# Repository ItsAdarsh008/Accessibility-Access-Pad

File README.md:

# AccessibilityAccessPad by Adarsh

AAPad is an 8 key macropad with a rotary encoder, an OLED Display. It also has 9 WS2812B Leds, and uses QMK firmware

It serves as a plug & play device integrated with the Windows accessibility toolkit in order to allow computer-illiterate users use of accessibility features (i.e. high contrast mode). 

## Features:
- Dual layer PLA case (hopefully made out of wood, later)
- Plexiglass window, displaying the diodes and silkscreened logo on the PCB (also my glasses )
- 128x32 OLED Display, to allow bystanders to assist the user whenever necessary
- EC11 Rotary encoder, for tactile feedback
- 9 WS2812B RGB LEDs. One for the accessibility icon, and the rest for backlighting
- 8 Keys (for functions, see below)

## Planned Features:
- [VIA](https://www.caniusevia.com/) support!
- Reactive backlight for each key

## CAD Model:
Everything fits together using 6 M3 Bolts and heatset inserts. 4 for the case, two for the PCB.

It has 2 separate printed pieces. The base, where the PCB is mounted, and the cover.

Made in Fusion360. First time using it!

## PCB
Here's my PCB! It was made in KiCad. The silkscreen(s) was imported from Canva. I also put a quote on the top right, because why not?

Schematic

PCB

## Firmware Overview
This hackpad uses [QMK](https://qmk.fm/) firmware for everything. 

- The rotary encoder changes volume, press to mute

- The 8 keys currently act as functions/macros I preassigned in QMK.
    1. Text-to-Speech (TTS) Toggle
        - Reads aloud selected text on screen
    2. Zoom In
    3. Zoom Out
    4. Speech-to-Text Activation
        - Starts or stops dictation mode to convert speech into text
    5. Adjusts Cursor Speed
    6. Activates Computer speakers to announce a custom message (preset "I need assistance")
    7. High Contrast Mode Toggle
    8. Opens Accessibility Settings Window

- The OLED reads out the function of a button whenever it is pressed. The goal is so that any bystander who is called to assist the user may know what the device is suppose to be doing at any given input.

- *Note*: **Please suggest any new functions for each key!!** I have a very limited understanding of accessibility needs at the moment, though I hope my preset functions serve you well.

## BOM:
Here should be everything you need to make this hackpad

- 8x Cherry MX Style Switches
- 8x DSA Keycaps
- 6x M3x5x4 Heatset inserts
- 3x M3x16mm SHCS Bolts
- 9x 1N4148 DO-35 Diodes.
- 9x WS2812B LEDs
- 1x 0.91" 128x32 OLED Display
- 1x EC11 Rotary Encoder
- 1x XIAO RP2040
- 1x Case (2 printed parts, PLA)

## Extra stuff
Thanks so much for reading to the end, this is my first real hardware project. Stay tuned to my GitHub for more :\)\)

~ Adarsh

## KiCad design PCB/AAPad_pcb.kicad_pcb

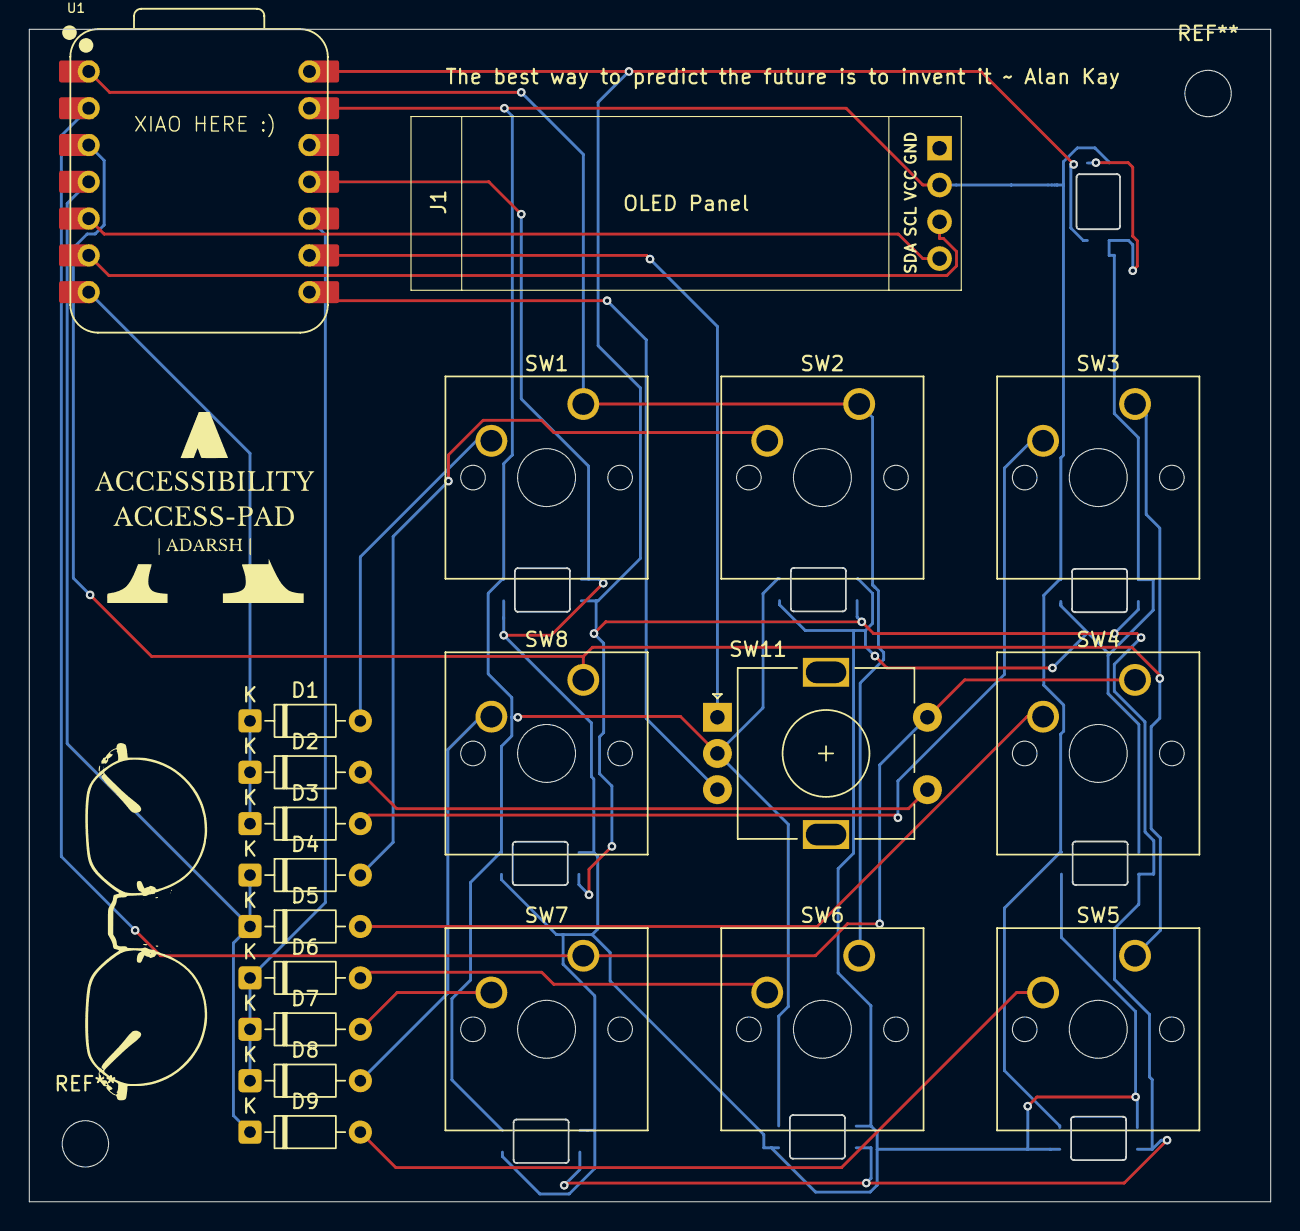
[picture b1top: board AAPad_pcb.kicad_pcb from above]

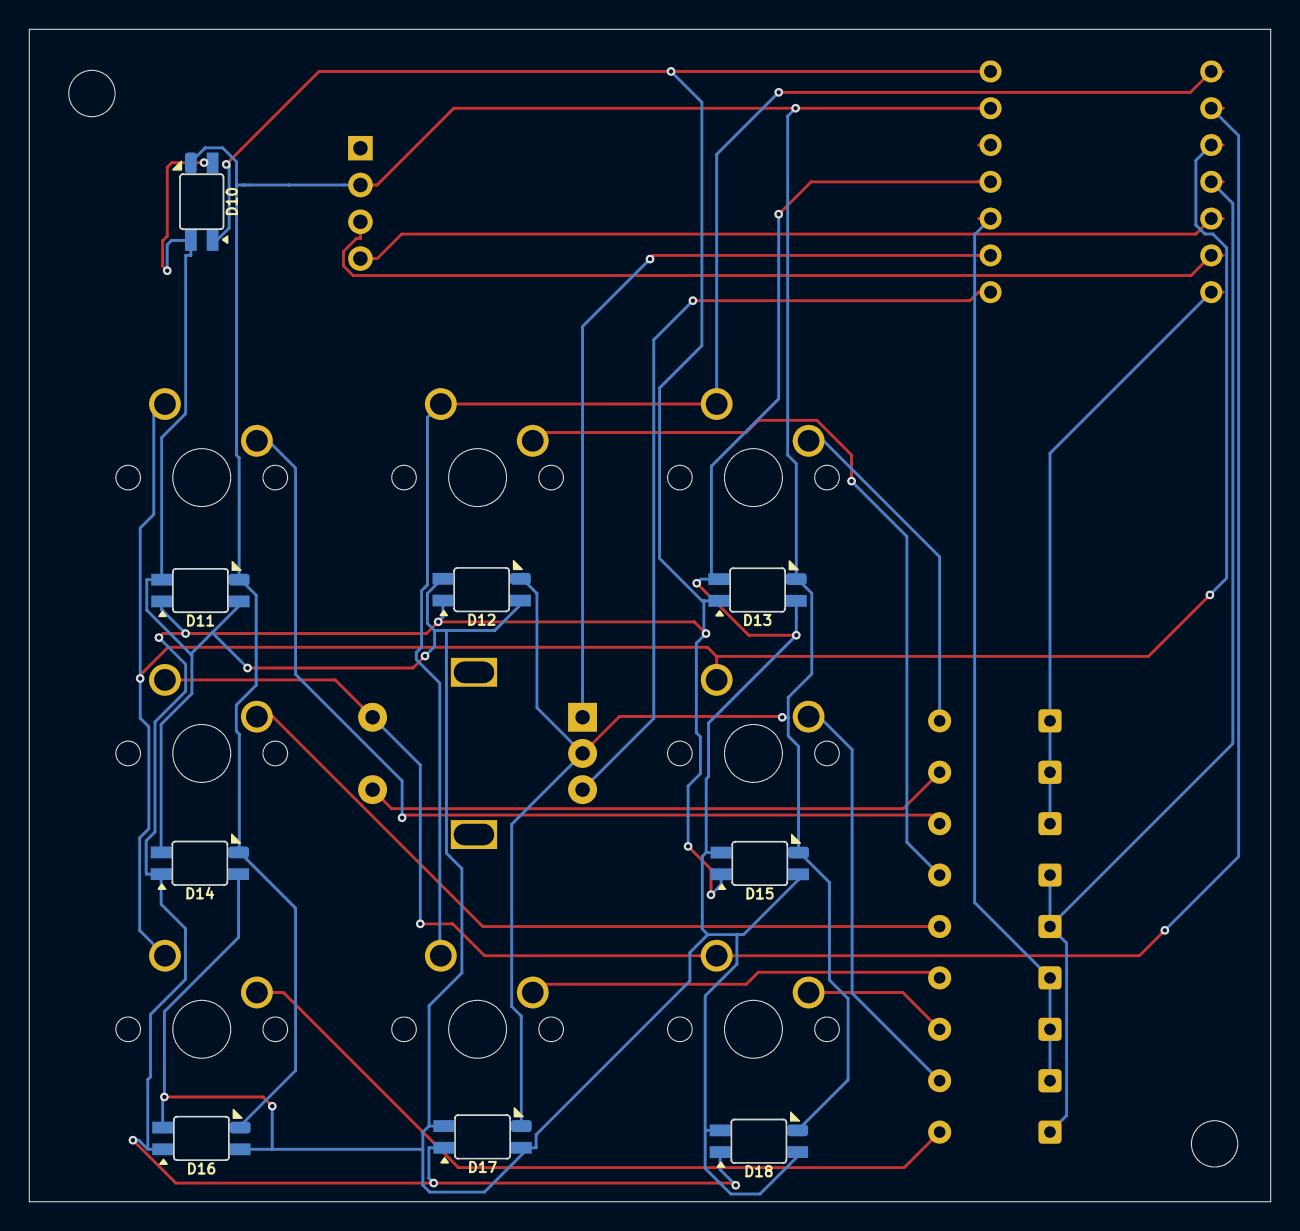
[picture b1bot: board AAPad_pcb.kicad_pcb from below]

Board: 2 copper layers, 85.7 x 81.0 mm, 29 parts (9 on the bottom side), 22 nets.

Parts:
D1, D2, D3, D4, D5, D6, D7, D8, D9: 1N4148WT; D_DO-35_SOD27_P7.62mm_Horizontal
D10, D11, D12, D13, D14, D15, D16, D17, D18: WS2812B; SK6812-MINI-E
J1: OLED_DISPLAY; SSD1306-0.91-OLED-4pin-128x32
SW1, SW2, SW3, SW4, SW5, SW6, SW7, SW8: SW_Push_45deg; SW_Cherry_MX_1.00u_PCB
SW11: RotaryEncoder_Switch; RotaryEncoder_Alps_EC11E-Switch_Vertical_H20mm
U1: XIAO-RP2040-DIP

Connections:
+5V: D10.1 (VDD), D11.1 (VDD), D12.1 (VDD), D13.1 (VDD), D14.1 (VDD), D15.1 (VDD), D16.1 (VDD), D17.1 (VDD), D18.1 (VDD), U1.14 (VBUS)
Col 0: SW1.1, SW2.1, SW6.1, U1.1 (GPIO26/ADC0/A0)
Col 1: SW4.1, SW7.1, SW11.S2, U1.2 (GPIO27/ADC1/A1)
Col 2: SW3.1, SW5.1, SW8.1, U1.3 (GPIO28/ADC2/A2)
EC11A: SW11.A, U1.9 (GPIO2/SCK)
EC11B: SW11.B, U1.8 (GPIO1/RX)
EC11SWB: D2.2 (A), SW11.S1
GND: D10.3 (VSS), D11.3 (VSS), D12.3 (VSS), D13.3 (VSS), D14.3 (VSS), D15.3 (VSS), D16.3 (VSS), D17.3 (VSS), D18.3 (VSS), J1.2, SW11.C, U1.13 (GND)
unnamed: D1.2 (A), SW1.2
unnamed: D3.2 (A), SW3.2
unnamed: D4.2 (A), SW2.2
unnamed: D5.2 (A), SW4.2
unnamed: D6.2 (A), SW6.2
unnamed: D7.2 (A), SW7.2
unnamed: D8.2 (A), SW8.2
unnamed: D9.2 (A), SW5.2
Row 0: D4.1 (K), D5.1 (K), D9.1 (K), U1.4 (GPIO29/ADC3/A3)
Row 1: D1.1 (K), D2.1 (K), D3.1 (K), U1.7 (GPIO0/TX)
Row 2: D6.1 (K), D7.1 (K), D8.1 (K), U1.10 (GPIO4/MISO)
SCL: J1.3, U1.6 (GPIO7/SCL)
SDA: J1.4, U1.5 (GPIO6/SDA)
WS2812B: D10.2 (DOUT), D10.4 (DIN), D11.2 (DOUT), D11.4 (DIN), D12.2 (DOUT), D12.4 (DIN), D13.2 (DOUT), D13.4 (DIN), D14.2 (DOUT), D14.4 (DIN), D15.2 (DOUT), D15.4 (DIN), D16.2 (DOUT), D16.4 (DIN), D17.2 (DOUT), D17.4 (DIN), D18.2 (DOUT), D18.4 (DIN), U1.11 (GPIO3/MOSI)

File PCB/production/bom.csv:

Designator,Footprint,Quantity,Value,LCSC Part #
"D1, D2, D3, D4, D5, D6, D7, D8, D9",D_DO-35_SOD27_P7.62mm_Horizontal,9,1N4148WT,
"D10, D11, D12, D13, D14, D15, D16, D17, D18",SK6812-MINI-E,9,WS2812B,
J1,SSD1306-0.91-OLED-4pin-128x32,1,OLED_DISPLAY,
"SW1, SW2, SW3, SW4, SW5, SW6, SW7, SW8",SW_Cherry_MX_1.00u_PCB,8,SW_Push_45deg,
SW11,RotaryEncoder_Alps_EC11E-Switch_Vertical_H20mm,1,RotaryEncoder_Switch,
U1,XIAO-RP2040-DIP,1,XIAO-RP2040-DIP,

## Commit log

2025-07-10 PCB folder filled in, now awaiting final CAD designs
2025-07-10 added js test file
2025-07-10 removed js file again, to test
2025-07-10 updated CAD file format, added texture for aesthetics
2025-07-10 updated the names of the pcb files for professionalism
2025-07-10 added firmware from QMK
2025-07-11 Added Gerber Files for Production, ReadMe complete
2025-07-11 fixed images in README.md
2025-07-11 added case production files, compiled firmware
2025-07-11 zipped gerber file
2025-07-11 updated production files to fit JLPCB requirements
2025-07-11 updated production files once again
2025-07-12 added PCB Backups and slightly altered constraints for PCB
2025-07-12 merged branches
